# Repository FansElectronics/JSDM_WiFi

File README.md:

# Jadwal Sholat Dot Matrix (JSDM) P10 dengan ESP8266 & ESP32

Firmware display Jadwal Waktu Sholat dengan tampilan Panel P10 Dot Matrix Display (DMD) menggunakan mikrokontroler ESP8266 dan ESP32. Project ini dirancang untuk menjalankan sebuah sistem dan perhitungan jadwal sholat di Indonesia. Sudah didukung dengan pengaturan dengan aplikasi Android yang dapat di download di: https://play.google.com/store/apps/details?id=com.fanselectronics.jsdm&hl=id

## Spesifikasi Firmware ⚙️:
- Mendukung Mikrokontroler ESP8266 dan ESP32
- Mendukung RTC DS3231
- Mendukung Panel P10 Single Color
- Menggunakan catu daya 5V (disesuaikan panel)
- Pengaturan melalui aplikasi Android
- 1 baris Panel x Maksimal 6 kolom Panel (disesuaikan lisensi)

## Fitur yang tersedia ✅:
- Animasi Jadwal Waktu Sholat (tersida beberapa model animasi sesuai pilihan jumlah panel)
- Animasi pesan running text (custom melalui aplikasi android)
- Logo Allah & Muhammad (tersida beberapa model logo)
- Sleep Mode saat malam hari tidak terpakai
- Kalendar Masehi, Hijriah, dan Jawa (Pasaran, Wuku, dan Tahun menurut kalendar Agungan)
- Alarm / Alert waktu Adzan
- Waktu hitung mundur Qobliyah setelah Adzan dan tunggu Iqomah
- Pengaturan waktu Iqomah setiap sholat
- Sleep Mode waktu sholat
- Sleep Mode waktu khotbah Jum'at
- Upload **license.json** melalui aplikasi android
- Update firmware On the Air (OTA), update firmware lebih mudah via internet

_**Catatan:** fitur dan animasi akan selalu diupdate, anda bisa update firmware terbaru dengan mudah melalui fitur OTA di aplikasi android._

## Default SSID + Password
```
    SSID: JSDM WiFi
    PASS: fanselectronics
```

## Mengapa dimulai dari versi 3?

Sebelumnya project ini bersifat private saja dengan membuka firmware dan mengimplementasikan sistem lisensi, siapapun dapat membuat sendiri dan hanya tinggal membeli lisensi firmwarenya saja dengan mudah dan murah.

## Bagaimana Sistem Lisensinya?

Kami mengimplementasikan sistem lisensi terenkripsi berbasis **Identifikasi Hardware** unik. Setiap ESP8266 dan ESP32 memiliki ID Unik yang tidak dapat ditukarkan, jadi pembeli tinggal mengirimkan **Device ID** yang tersedia pada menu activation aplikasi setelah aplikasi terhubung ke perangkat dan kami akan mengirimkan file **license.json** yang dapat diupload ke perangkat melalui fitur **Activation** di aplikasi Android.

Menengapa lisensi harus berbayar? tentunya kami membutuhkan dana untuk keperluan riset dan biaya hidup, permintaan ini juga memberikan kami semangat untuk terus memelihara dan perbarui fitur-fitur pada firmware dari JSDM WiFi Android ini. Sehingga mohon pengertiannya.

**Adapun Harga Lisensi dibedakan berdasarkan jumlah panel sebagai berikut 🏷️:**
- 1x1 Panel : Rp. 40,000
- 2x1 Panel : Rp. 60,000
- 3x1 Panel : Rp. 80,000 
- 4x1 Panel : Rp. 100,000 
- 5x1 Panel : _Next Update_
- 6x1 Panel : _Next Update_
- 1x2 Panel : _Next Update_
- 2x2 Panel : _Next Update_
- 3x2 Panel : _Next Update_
- 4x2 Panel : _Next Update_
- 5x2 Panel : _Next Update_
- 6x2 Panel : _Next Update_

_Catatan: Jumlah panel akan diupdate terus dimasa yang akan datang. ukuran panel kolom x baris._

**Fitur Auto Murottal**

Fitur auto murottal berbasis wireless dimana membutuhkan tambahan module JSAM Auto Murottal yang  dijalakan dalam mode Slave Mode (Tanpa Lisensi) otomatis akan terhubung dengan perangkat JSDM dengan komunikasi Wireless (ESP Now). 

- Update Fitur Auto Murottal : Rp.95,000 (Belum termasuk module Auto Murottalnya)
- Baca detail terkait fitur JSAM Auto Murottal di https://github.com/FansElectronics/JSAM_Auto_Murottal

_Catatan: Anda dapat membuat sendiri module murottal atau membeli langsung kepada kami_

**Syarat dan Ketentuan Lisensi 📜:** 
- Lisensi berlaku mutlak untuk 1 (satu) chip ESP8266 atau ESP32 karena mengikat berdasarkan ID unik perangkat keras.
- Lisensi berlaku untuk konfigurasi parameter yang disepakati, perubahan menyesuaikan harga.
- Pernyesuaian perameter downgrade tidak dapat mengembalikan selisi biaya dari lisensi awal yang sudah dikirim.
- Pernyesuaian perameter upgrade harus menambahkan biaya selisi tambahan dari versi bawah.
- Garansi lisensi berlaku apabila chip rusak secara fisik dan kirim chip rusak kepada kami sebagai bukti. Jika chip tidak dapat dikirim, wajib membeli lisensi baru.
- Garansi berlaku 1 tahun dari license diterbitkan.
- Pembelian pihak kedua/ketiga tetap dilayani sesuai syarat di atas selama ID unik terdaftar resmi di database kami.

## Sistem pembayaran 💵

Kami memberikan 2 sistem pembayaran dimana sistem donasi dan pembayaran sesuai harga tertera. Anda dapat menggunakan sistem donasi apabila ingin memberikan support kepada kami melebihi harga lisensi yang ada.
- Pembelian dan Bantuan: https://wa.me/6281803750001
- Donasi: https://saweria.co/fanselectronics

## Bagaimana Upload Firmwarenya❓
Kami telah menyediakan tool untuk upload / flash chip ES8266 dan ESP32 yang memudahkan siapapun untuk membuat project ini secara mandiri. Berikut url tool JSDM WiFi Flasher:
- JSDM Firmware Flasher : https://app.fanselectronics.com/flasher/JSDM/
- License Uploader : https://app.fanselectronics.com/tools/license-uploader
- Tutorialnya bisa baca di [FLASHER.md](FLASHER.md)

## Skematik dan PCB 💾
Semua file Skematik dan PCB saya sediakan gratis di dalam repository ini dalam bentuk desain apliksi EAGLE PCB hingga export PDF. Sesuaikan dengan board yang anda gunakan atau anda bisa mengkustomisasi sesuai dengan keinginan anda dengan panduan pin I/O yang sudah disediakan.

### Skematik WEMOS D1 Mini HUB12 & HUB08

### Skematik WEMOS D1 Mini 3x HUB12

### Skematik ESP32 Devkit HUB12 & HUB08

### Skematik ESP32 Devkit 3x HUB12

## Tutorial & Video 🎥

## Terima Kasih Kepada 🤲
- Allah Subhanahu Wa Ta'ala
- Arduino.cc
- GitHub
- Kontributor
- Semua orang yang mentraktir saya kopi

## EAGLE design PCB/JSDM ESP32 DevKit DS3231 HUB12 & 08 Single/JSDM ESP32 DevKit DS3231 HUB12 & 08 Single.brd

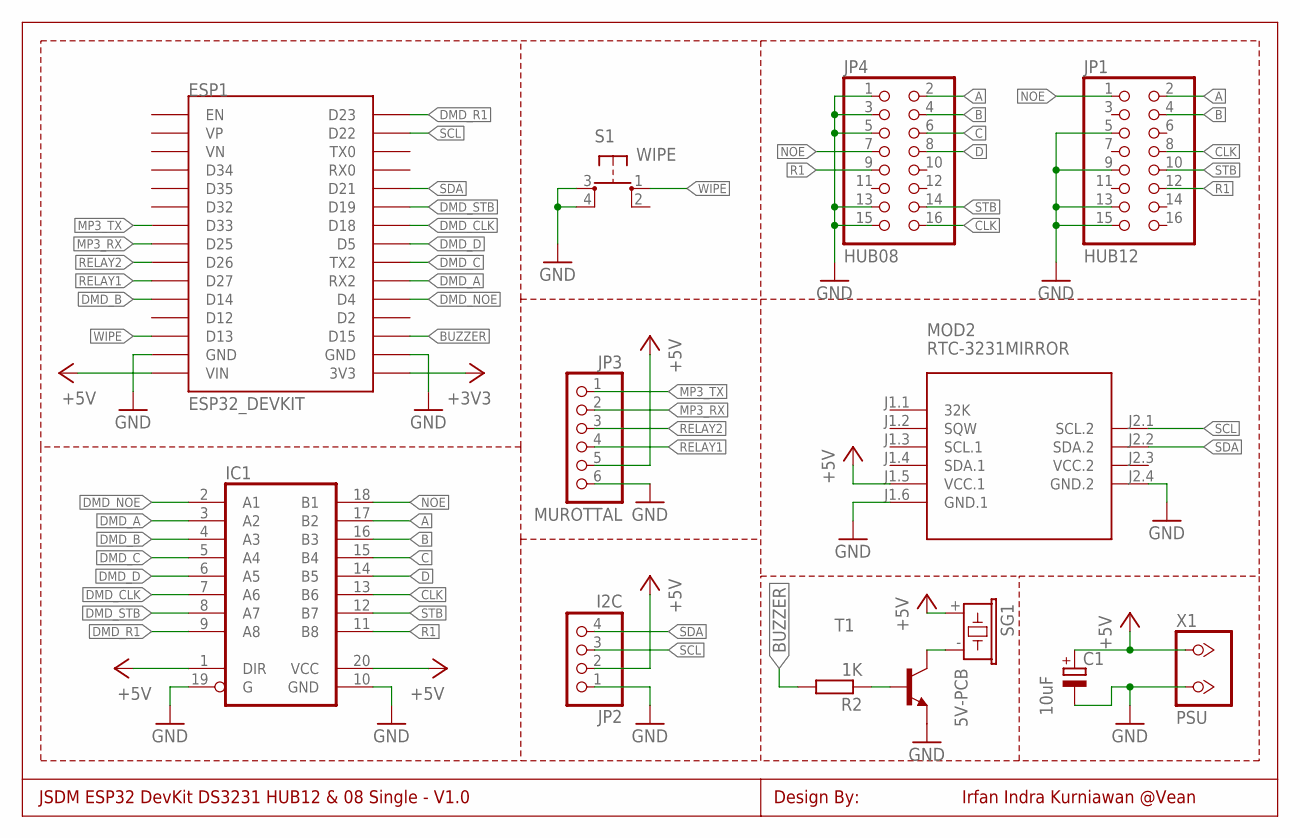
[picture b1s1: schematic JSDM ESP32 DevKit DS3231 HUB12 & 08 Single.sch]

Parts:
C1: 10uF; E3,5-8
ESP1: ESP32_DEVKIT
IC1: 74245SMD; SO20
JP1: HUB12; 2X08
JP2: I2C; 1X04
JP3: MUROTTAL; 1X06
JP4: HUB08; 2X08
MOD2: RTC-3231MIRROR; RTC-DS3231-MIRROR
R2: 1K; 0207/10
S1: WIPE; TACT-6X6MM-OCTAGON
SG1: 5V-PCB; 5V
T1: BC317-NPN-TO92-EBC; TO92-EBC
X1: PSU; TB2

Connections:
+3V3: ESP1.3V3
+5V: C1.+, ESP1.VIN, IC1.1 (DIR), IC1.20 (VCC), JP2.2, JP3.5, MOD2.J1.5 (VCC.1), SG1.+ (1), X1.1
A: IC1.17 (B2), JP1.2, JP4.2
B: IC1.16 (B3), JP1.4, JP4.4
BUZZER: ESP1.D15, R2.2
C: IC1.15 (B4), JP4.6
CLK: IC1.13 (B6), JP1.8, JP4.16
D: IC1.14 (B5), JP4.8
DMD_A: ESP1.RX2, IC1.3 (A2)
DMD_B: ESP1.D14, IC1.4 (A3)
DMD_C: ESP1.TX2, IC1.5 (A4)
DMD_CLK: ESP1.D18, IC1.7 (A6)
DMD_D: ESP1.D5, IC1.6 (A5)
DMD_NOE: ESP1.D4, IC1.2 (A1)
DMD_R1: ESP1.D23, IC1.9 (A8)
DMD_STB: ESP1.D19, IC1.8 (A7)
GND: C1.-, ESP1.GND@1 (GND), ESP1.GND@2 (GND), IC1.10 (GND), IC1.19 (G), JP1.5, JP1.9, JP1.13, JP1.15, JP2.1, JP3.6, JP4.1, JP4.3, JP4.5, JP4.13, JP4.15, MOD2.J1.6 (GND.1), MOD2.J2.4 (GND.2), S1.3, S1.4 (P1), T1.E, X1.2
MP3_RX: ESP1.D25, JP3.2
MP3_TX: ESP1.D33, JP3.1
unnamed: SG1.- (2), T1.C
unnamed: R2.1, T1.B
NOE: IC1.18 (B1), JP1.1, JP4.7
R1: IC1.11 (B8), JP1.12, JP4.9
RELAY1: ESP1.D27, JP3.4
RELAY2: ESP1.D26, JP3.3
SCL: ESP1.D22, JP2.3, MOD2.J2.1 (SCL.2)
SDA: ESP1.D21, JP2.4, MOD2.J2.2 (SDA.2)
STB: IC1.12 (B7), JP1.10, JP4.14
VCC.2: MOD2.J2.3 (VCC.2)
WIPE: ESP1.D13, S1.1 (S)

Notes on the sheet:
JSDM ESP32 DevKit DS3231 HUB12 & 08 Single - V1.0
Irfan Indra Kurniawan @Vean
Design By:

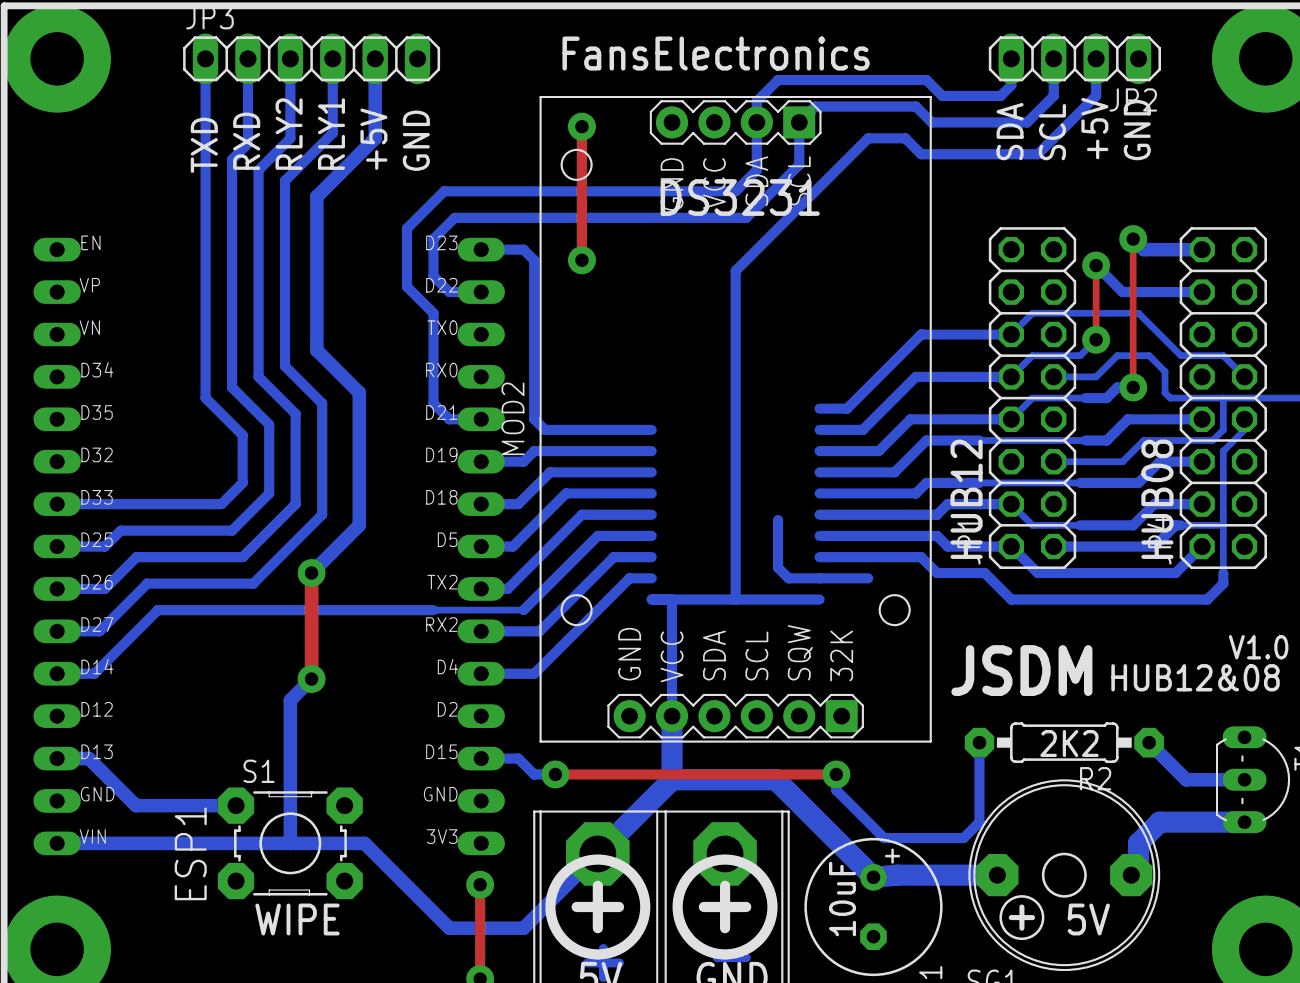
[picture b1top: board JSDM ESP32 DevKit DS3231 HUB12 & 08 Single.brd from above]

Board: 2 copper layers, 13 parts (1 on the bottom side), 28 nets.

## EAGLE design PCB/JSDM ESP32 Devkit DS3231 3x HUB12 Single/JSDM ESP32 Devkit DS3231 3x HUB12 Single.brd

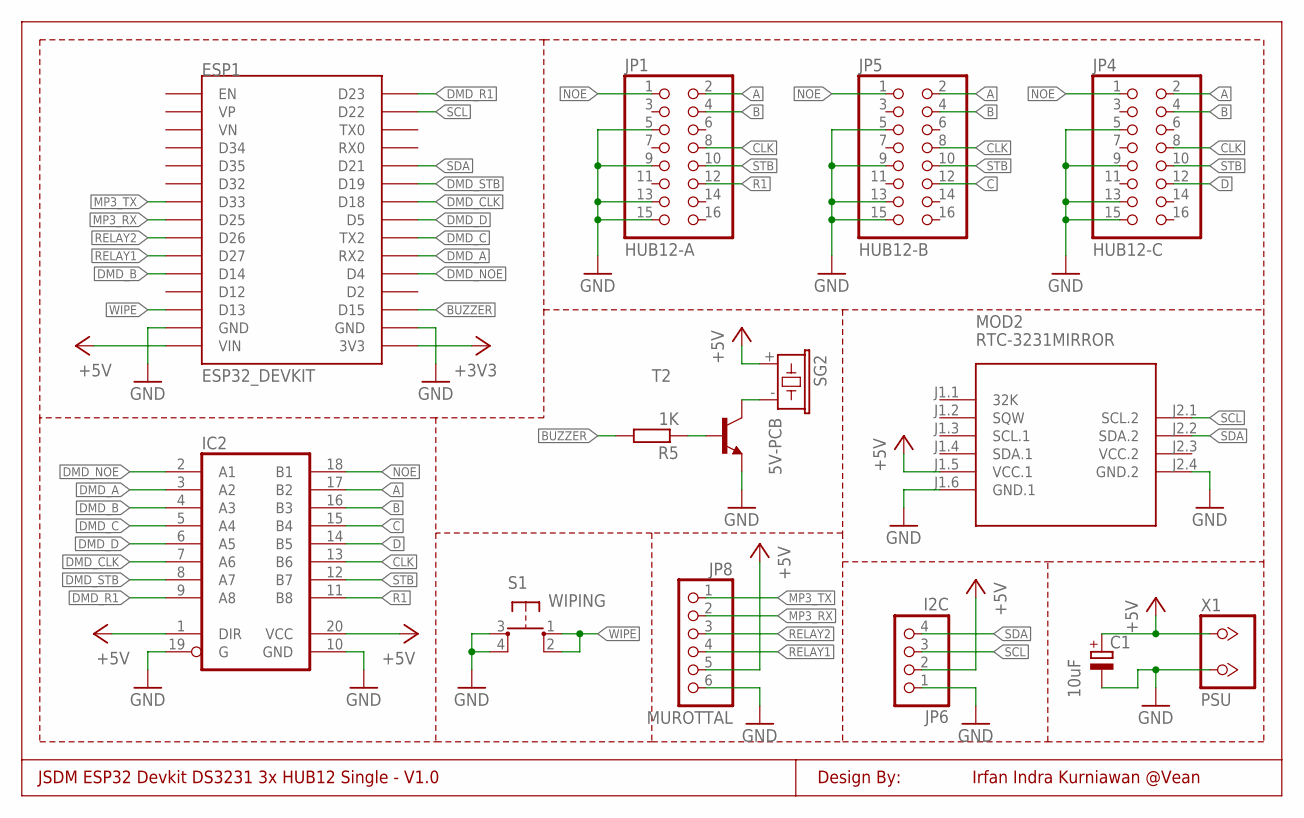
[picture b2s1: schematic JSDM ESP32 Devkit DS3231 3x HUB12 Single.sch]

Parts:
C1: 10uF; E3,5-8
ESP1: ESP32_DEVKIT
IC2: 74245SMD; SO20
JP1: HUB12-A; 2X08
JP4: HUB12-C; 2X08
JP5: HUB12-B; 2X08
JP6: I2C; 1X04
JP8: MUROTTAL; 1X06
MOD2: RTC-3231MIRROR; RTC-DS3231-MIRROR
R5: 1K; 0207/7
S1: WIPING; TACT-6X6MM-OCTAGON
SG2: 5V-PCB; 5V
T2: BC317-NPN-TO92-EBC; TO92-EBC
X1: PSU; TB2

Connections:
+3V3: ESP1.3V3
+5V: C1.+, ESP1.VIN, IC2.1 (DIR), IC2.20 (VCC), JP6.2, JP8.5, MOD2.J1.5 (VCC.1), SG2.+ (1), X1.1
A: IC2.17 (B2), JP1.2, JP4.2, JP5.2
B: IC2.16 (B3), JP1.4, JP4.4, JP5.4
BUZZER: ESP1.D15, R5.2
C: IC2.15 (B4), JP5.12
CLK: IC2.13 (B6), JP1.8, JP4.8, JP5.8
D: IC2.14 (B5), JP4.12
DMD_A: ESP1.RX2, IC2.3 (A2)
DMD_B: ESP1.D14, IC2.4 (A3)
DMD_C: ESP1.TX2, IC2.5 (A4)
DMD_CLK: ESP1.D18, IC2.7 (A6)
DMD_D: ESP1.D5, IC2.6 (A5)
DMD_NOE: ESP1.D4, IC2.2 (A1)
DMD_R1: ESP1.D23, IC2.9 (A8)
DMD_STB: ESP1.D19, IC2.8 (A7)
GND: C1.-, ESP1.GND@1 (GND), ESP1.GND@2 (GND), IC2.10 (GND), IC2.19 (G), JP1.5, JP1.9, JP1.13, JP1.15, JP4.5, JP4.9, JP4.13, JP4.15, JP5.5, JP5.9, JP5.13, JP5.15, JP6.1, JP8.6, MOD2.J1.6 (GND.1), MOD2.J2.4 (GND.2), S1.3, S1.4 (P1), T2.E, X1.2
MP3_RX: ESP1.D25, JP8.2
MP3_TX: ESP1.D33, JP8.1
unnamed: SG2.- (2), T2.C
unnamed: R5.1, T2.B
NOE: IC2.18 (B1), JP1.1, JP4.1, JP5.1
R1: IC2.11 (B8), JP1.12
RELAY1: ESP1.D27, JP8.4
RELAY2: ESP1.D26, JP8.3
SCL: ESP1.D22, JP6.3, MOD2.J2.1 (SCL.2)
SDA: ESP1.D21, JP6.4, MOD2.J2.2 (SDA.2)
STB: IC2.12 (B7), JP1.10, JP4.10, JP5.10
VCC.2: MOD2.J2.3 (VCC.2)
WIPE: ESP1.D13, S1.1 (S), S1.2 (S1)

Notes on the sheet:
JSDM ESP32 Devkit DS3231 3x HUB12 Single - V1.0
Irfan Indra Kurniawan @Vean
Design By:

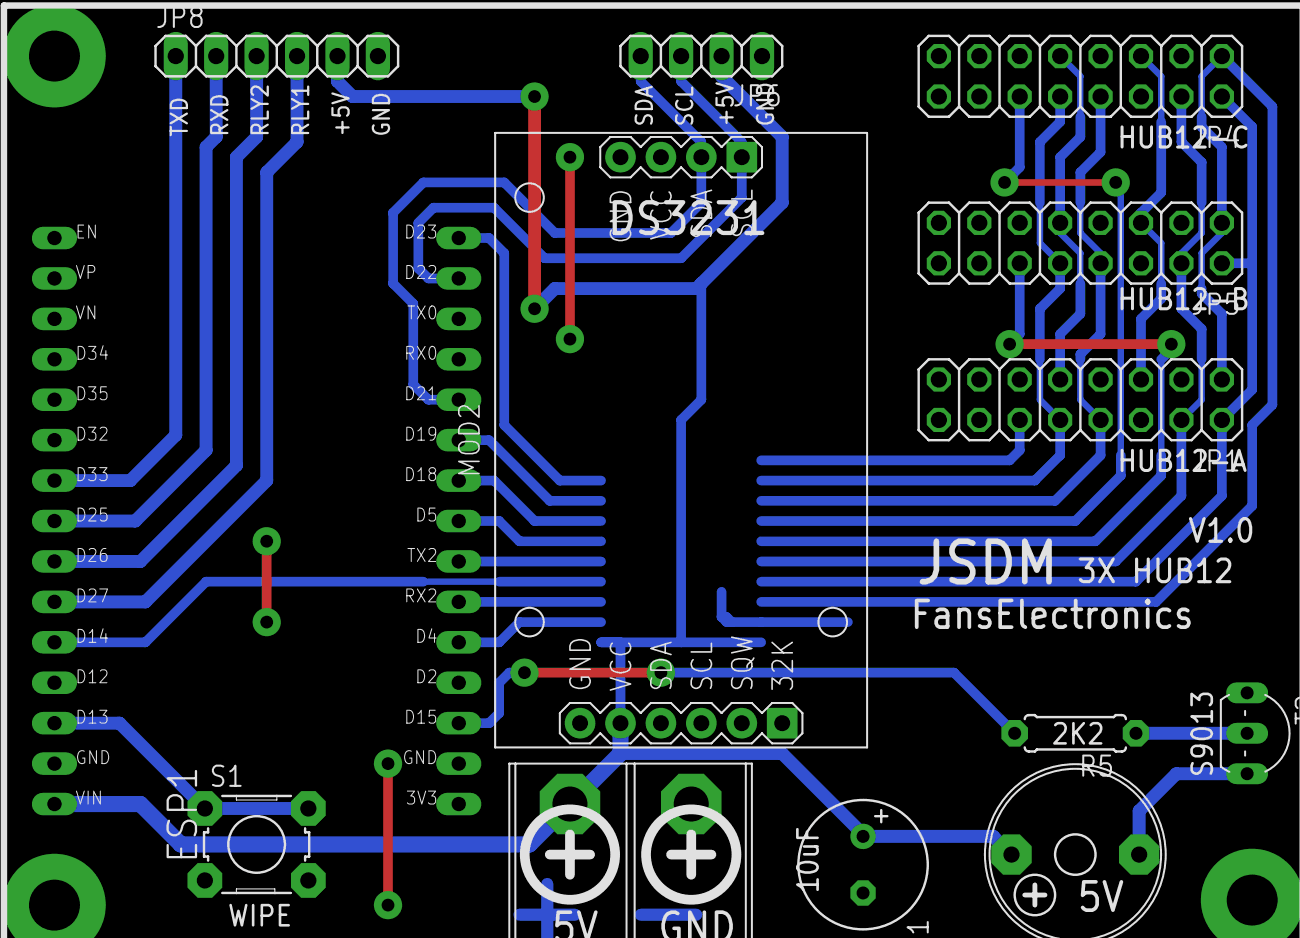
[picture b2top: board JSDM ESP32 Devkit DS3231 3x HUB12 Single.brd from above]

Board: 2 copper layers, 14 parts (1 on the bottom side), 28 nets.

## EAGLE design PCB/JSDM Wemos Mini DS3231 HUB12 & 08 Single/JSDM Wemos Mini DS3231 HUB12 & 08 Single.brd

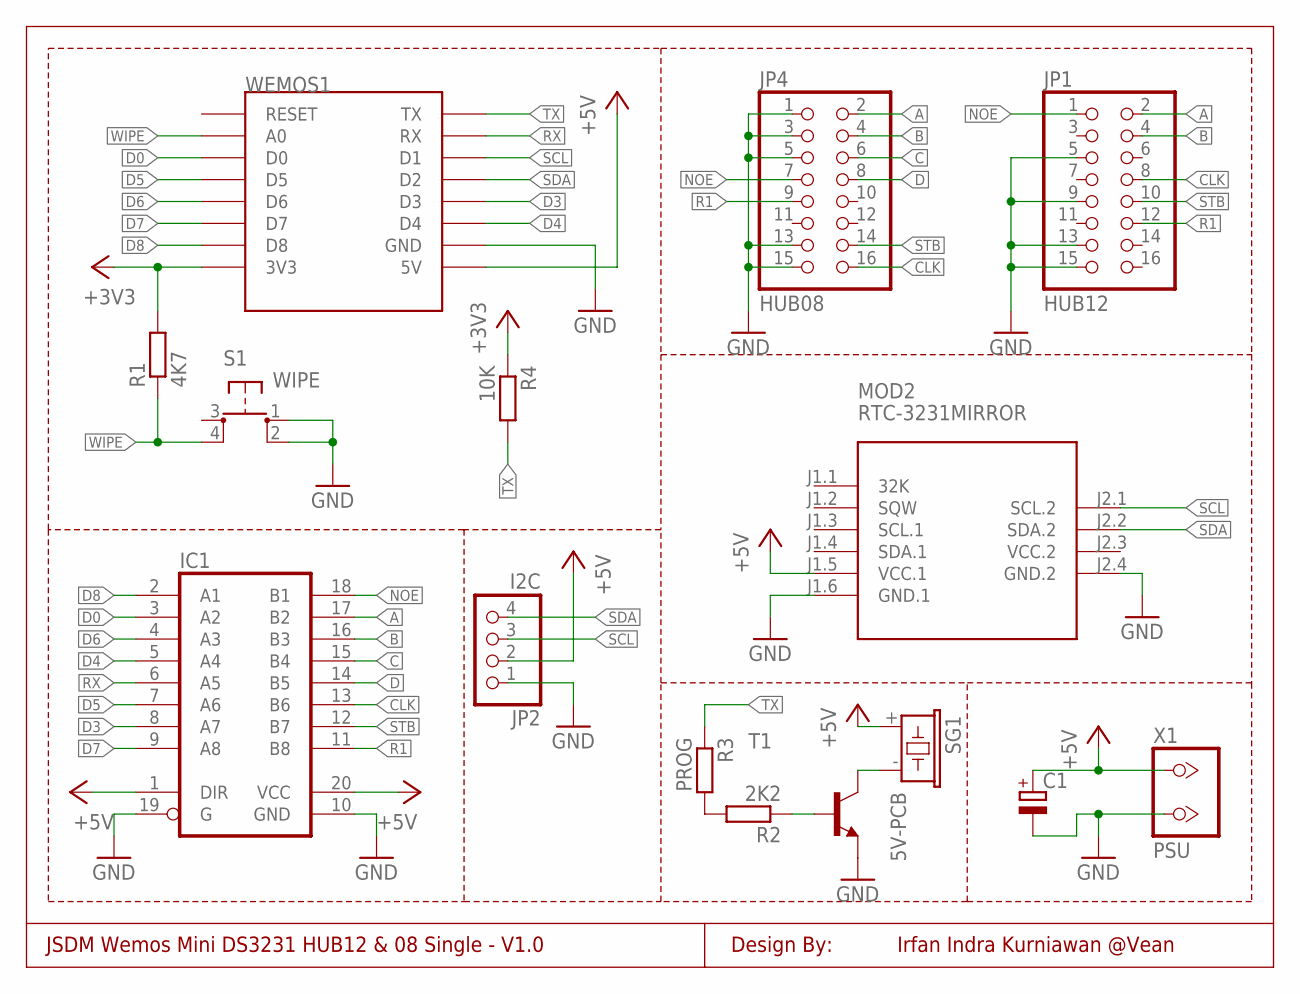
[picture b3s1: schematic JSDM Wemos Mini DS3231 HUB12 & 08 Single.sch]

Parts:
C1: CPOL-EUE3.5-8; E3,5-8
IC1: 74245SMD; SO20
JP1: HUB12; 2X08
JP2: I2C; 1X04
JP4: HUB08; 2X08
MOD2: RTC-3231MIRROR; RTC-DS3231-MIRROR
R1: 4K7; 0207/12
R2: 2K2; 0207/7
R3: PROG; M0805
R4: 10K; 0207/12
S1: WIPE; TACT-6X6MM-OCTAGON
SG1: 5V-PCB; 5V
T1: BC317-NPN-TO92-EBC; TO92-EBC
WEMOS1: WEMOS-D1-MINI
X1: PSU; TB2

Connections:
+3V3: R1.2, R4.1, WEMOS1.3V3
+5V: C1.+, IC1.1 (DIR), IC1.20 (VCC), JP2.2, MOD2.J1.5 (VCC.1), SG1.+ (1), WEMOS1.5V, X1.1
A: IC1.17 (B2), JP1.2, JP4.2
B: IC1.16 (B3), JP1.4, JP4.4
C: IC1.15 (B4), JP4.6
CLK: IC1.13 (B6), JP1.8, JP4.16
D: IC1.14 (B5), JP4.8
D0: IC1.3 (A2), WEMOS1.D0
D3: IC1.8 (A7), WEMOS1.D3
D4: IC1.5 (A4), WEMOS1.D4
D5: IC1.7 (A6), WEMOS1.D5
D6: IC1.4 (A3), WEMOS1.D6
D7: IC1.9 (A8), WEMOS1.D7
D8: IC1.2 (A1), WEMOS1.D8
GND: C1.-, IC1.10 (GND), IC1.19 (G), JP1.5, JP1.9, JP1.13, JP1.15, JP2.1, JP4.1, JP4.3, JP4.5, JP4.13, JP4.15, MOD2.J1.6 (GND.1), MOD2.J2.4 (GND.2), S1.1 (S), S1.2 (S1), T1.E, WEMOS1.GND, X1.2
unnamed: SG1.- (2), T1.C
unnamed: R2.1, T1.B
unnamed: R2.2, R3.2
NOE: IC1.18 (B1), JP1.1, JP4.7
R1: IC1.11 (B8), JP1.12, JP4.9
RX: IC1.6 (A5), WEMOS1.RX
SCL: JP2.3, MOD2.J2.1 (SCL.2), WEMOS1.D1
SDA: JP2.4, MOD2.J2.2 (SDA.2), WEMOS1.D2
STB: IC1.12 (B7), JP1.10, JP4.14
TX: R3.1, R4.2, WEMOS1.TX
VCC.2: MOD2.J2.3 (VCC.2)
WIPE: R1.1, S1.4 (P1), WEMOS1.A0

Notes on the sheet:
JSDM Wemos Mini DS3231 HUB12 & 08 Single - V1.0
Irfan Indra Kurniawan @Vean
Design By:

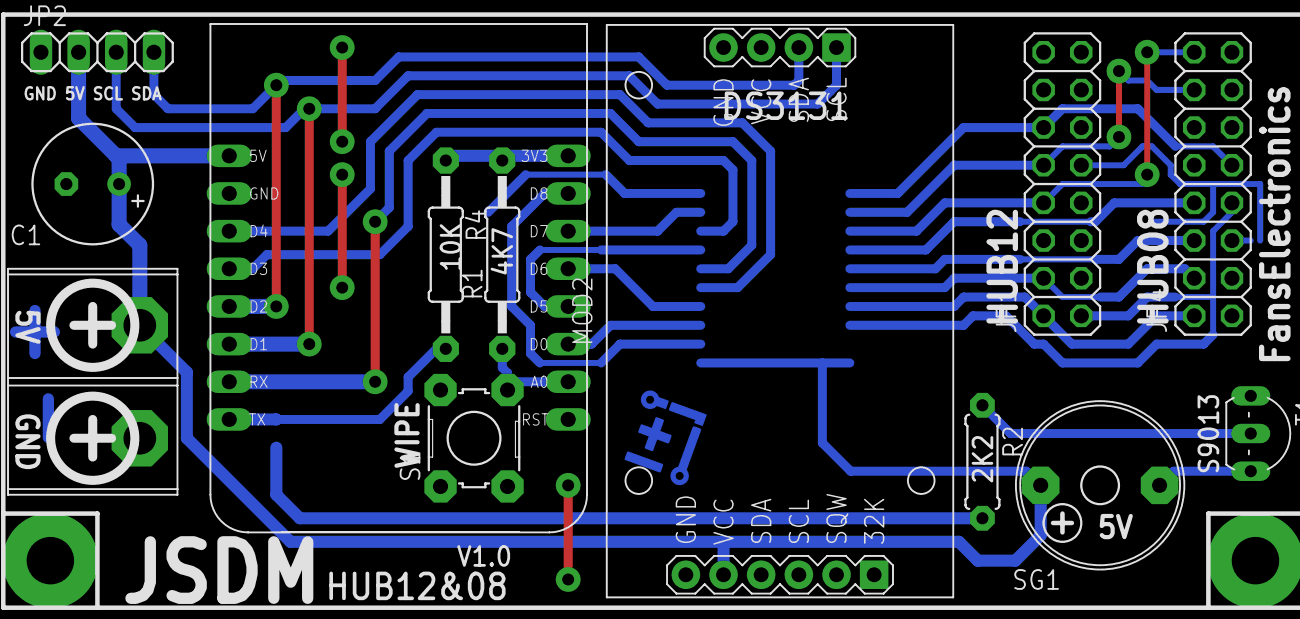
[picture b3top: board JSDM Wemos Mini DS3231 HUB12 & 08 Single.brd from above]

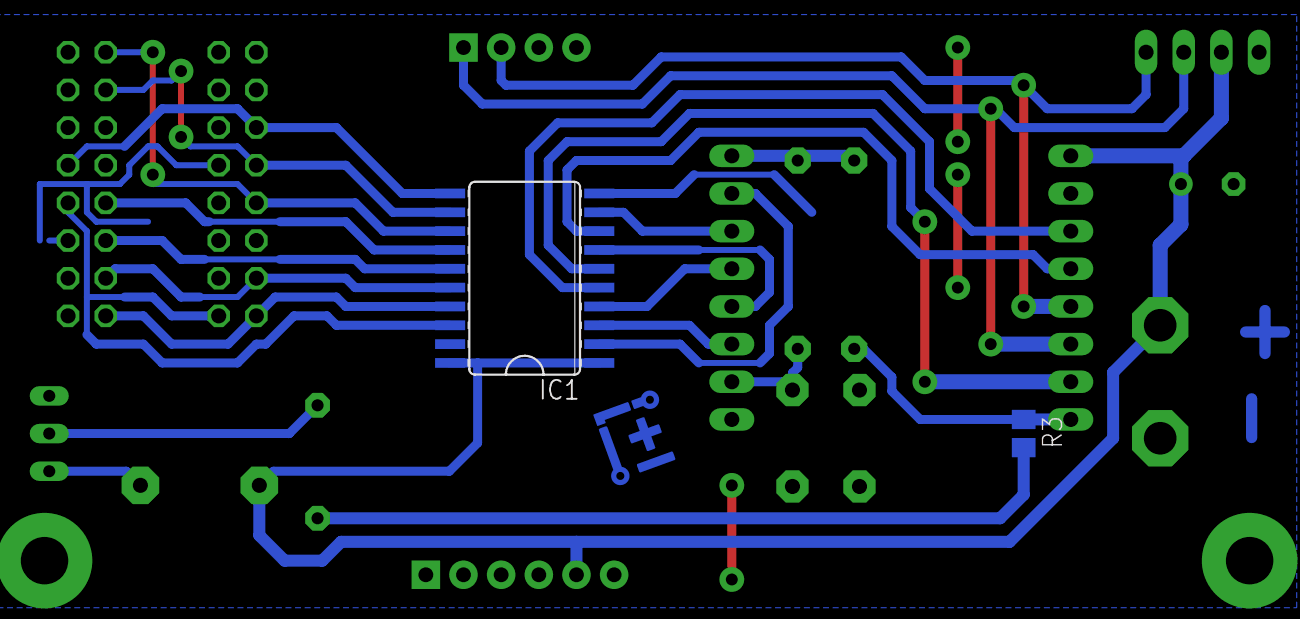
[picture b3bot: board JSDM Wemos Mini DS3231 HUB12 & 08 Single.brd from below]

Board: 2 copper layers, 15 parts (2 on the bottom side), 26 nets.
